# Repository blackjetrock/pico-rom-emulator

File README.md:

# pico-rom-emulator
ROM Emulator using Pico

This is a ROM emulator using a Raspberry Pi Pico to do the emulation in firmware.
The emulator is a small program that presents data on 8 data lines depending on the state of 16 address lines.
As the emulation is done in firmware there is a limit to the speed of ROm that can be emulated.
This has been teste on a 900kHz 6303 system (Psion Organiser) and also a 2MHz 6502 system. It may be able to run faster
and with overclocking faster than the standard clock rate can handle. 
As emulation is in firmware you get an extra for free, namely an address tracing facility. It can be set to start on any address, all setup is done
using the code itself and the trace is accessed through a debugger, I use Eclipse.

The emulation currently runs on the second core of the RP2040, as I was having problems with the interrupts on core0 mucking up
the emulation, turning interrupts off was a problem as download didn't work well. Using core 1 seems to be a better solution. It may even be possible to 
run a USB serial monitor of some kind on core 0 while emulating. I haven't got round ot this yet.

There's a PCB in the repo too, which is a Pico and some level shifters to allow the emulator to run on a 5V system when the Pico is 3V3. The data direction
is under firmware control. I have been using the emulator configured with a hardware OE which menas the OE signal to the ROM goes to the CE of the level
shifters. Placing data on the bus is therefore under hardware control. The PCB can be configured in other ways but I've not tried that.

This is a work in progress, but I have used it to get traces for stuff I've been working on.

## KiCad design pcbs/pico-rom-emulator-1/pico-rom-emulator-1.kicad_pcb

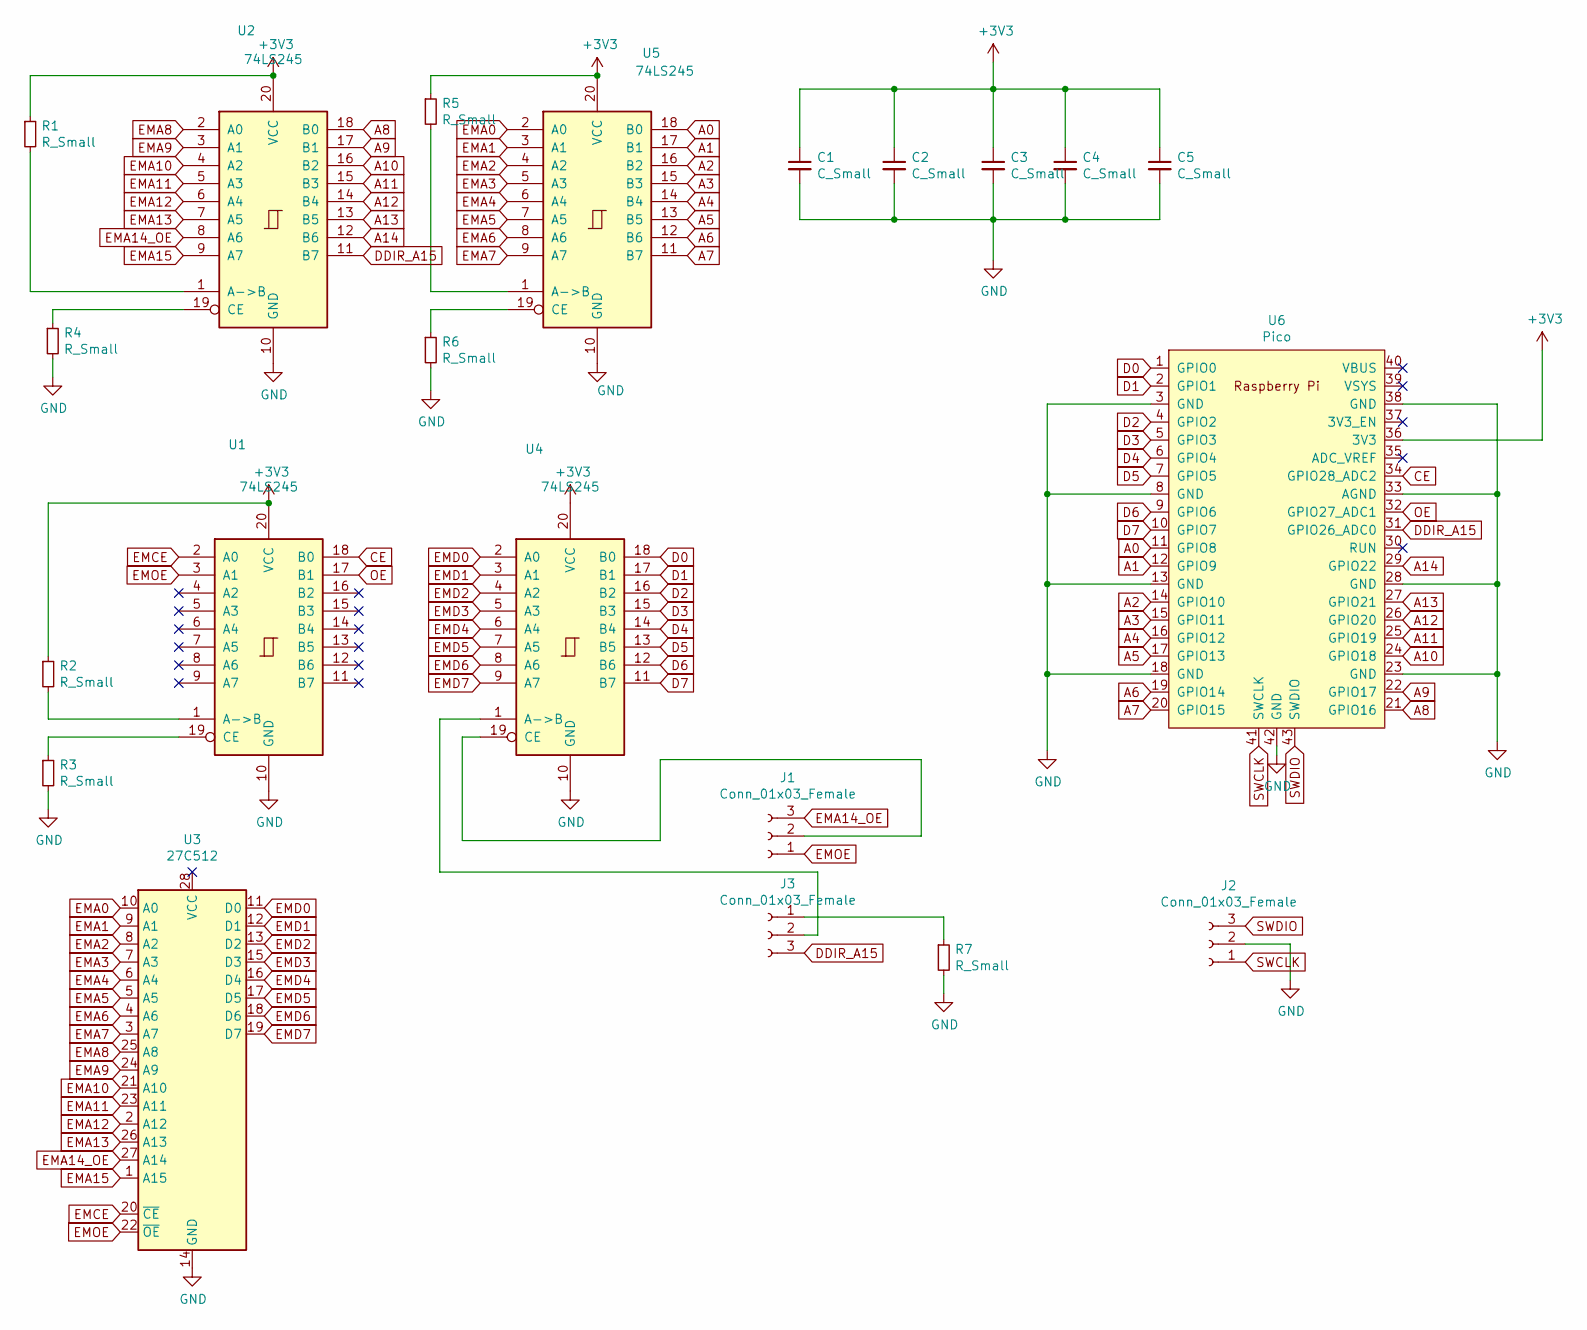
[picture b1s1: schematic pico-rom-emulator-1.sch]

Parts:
C1, C2, C3, C4, C5: C_Small; C_0805_2012Metric_Pad1.15x1.40mm_HandSolder
J1, J2, J3: Conn_01x03_Female; PinHeader_1x03_P2.54mm_Vertical
R1, R2, R3, R4, R5, R6, R7: R_Small; R_0805_2012Metric_Pad1.15x1.40mm_HandSolder
U1, U2, U4, U5: 74LS245; SOIC-20W_7.5x12.8mm_P1.27mm
U3: 27C512; DIP-28_W15.24mm
U6: Pico; RPi_Pico_SMD_TH

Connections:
+3V3: C1.1, C2.1, C3.1, C4.1, C5.1, R1.1, R2.1, R5.1, U1.20 (VCC), U2.20 (VCC), U4.20 (VCC), U5.20 (VCC), U6.36 (3V3)
A0: U5.18 (B0), U6.11 (GPIO8)
A1: U5.17 (B1), U6.12 (GPIO9)
A2: U5.16 (B2), U6.14 (GPIO10)
A3: U5.15 (B3), U6.15 (GPIO11)
A4: U5.14 (B4), U6.16 (GPIO12)
A5: U5.13 (B5), U6.17 (GPIO13)
A6: U5.12 (B6), U6.19 (GPIO14)
A7: U5.11 (B7), U6.20 (GPIO15)
A8: U2.18 (B0), U6.21 (GPIO16)
A9: U2.17 (B1), U6.22 (GPIO17)
A10: U2.16 (B2), U6.24 (GPIO18)
A11: U2.15 (B3), U6.25 (GPIO19)
A12: U2.14 (B4), U6.26 (GPIO20)
A13: U2.13 (B5), U6.27 (GPIO21)
A14: U2.12 (B6), U6.29 (GPIO22)
CE: U1.18 (B0), U6.34 (GPIO28_ADC2)
D0: U4.18 (B0), U6.1 (GPIO0)
D1: U4.17 (B1), U6.2 (GPIO1)
D2: U4.16 (B2), U6.4 (GPIO2)
D3: U4.15 (B3), U6.5 (GPIO3)
D4: U4.14 (B4), U6.6 (GPIO4)
D5: U4.13 (B5), U6.7 (GPIO5)
D6: U4.12 (B6), U6.9 (GPIO6)
D7: U4.11 (B7), U6.10 (GPIO7)
DDIR_A15: J3.3, U2.11 (B7), U6.31 (GPIO26_ADC0)
EMA0: U3.10 (A0), U5.2 (A0)
EMA1: U3.9 (A1), U5.3 (A1)
EMA2: U3.8 (A2), U5.4 (A2)
EMA3: U3.7 (A3), U5.5 (A3)
EMA4: U3.6 (A4), U5.6 (A4)
EMA5: U3.5 (A5), U5.7 (A5)
EMA6: U3.4 (A6), U5.8 (A6)
EMA7: U3.3 (A7), U5.9 (A7)
EMA8: U2.2 (A0), U3.25 (A8)
EMA9: U2.3 (A1), U3.24 (A9)
EMA10: U2.4 (A2), U3.21 (A10)
EMA11: U2.5 (A3), U3.23 (A11)
EMA12: U2.6 (A4), U3.2 (A12)
EMA13: U2.7 (A5), U3.26 (A13)
EMA14_OE: J1.3, U2.8 (A6), U3.27 (A14)
EMA15: U2.9 (A7), U3.1 (A15)
EMCE: U1.2 (A0), U3.20 (~CE)
EMD0: U3.11 (D0), U4.2 (A0)
EMD1: U3.12 (D1), U4.3 (A1)
EMD2: U3.13 (D2), U4.4 (A2)
EMD3: U3.15 (D3), U4.5 (A3)
EMD4: U3.16 (D4), U4.6 (A4)
EMD5: U3.17 (D5), U4.7 (A5)
EMD6: U3.18 (D6), U4.8 (A6)
EMD7: U3.19 (D7), U4.9 (A7)
EMOE: J1.1, U1.3 (A1), U3.22 (~OE)
GND: C1.2, C2.2, C3.2, C4.2, C5.2, J2.2, R3.2, R4.2, R6.2, R7.2, U1.10 (GND), U2.10 (GND), U3.14 (GND), U4.10 (GND), U5.10 (GND), U6.3 (GND), U6.8 (GND), U6.13 (GND), U6.18 (GND), U6.23 (GND), U6.28 (GND), U6.33 (AGND), U6.38 (GND), U6.42 (GND)
unnamed: J1.2, U4.19 (CE)
unnamed: J3.1, R7.1
unnamed: J3.2, U4.1 (A->B)
unnamed: R1.2, U2.1 (A->B)
unnamed: R2.2, U1.1 (A->B)
unnamed: R3.1, U1.19 (CE)
unnamed: R4.1, U2.19 (CE)
unnamed: R5.2, U5.1 (A->B)
unnamed: R6.1, U5.19 (CE)
OE: U1.17 (B1), U6.32 (GPIO27_ADC1)
SWCLK: J2.1, U6.41 (SWCLK)
SWDIO: J2.3, U6.43 (SWDIO)

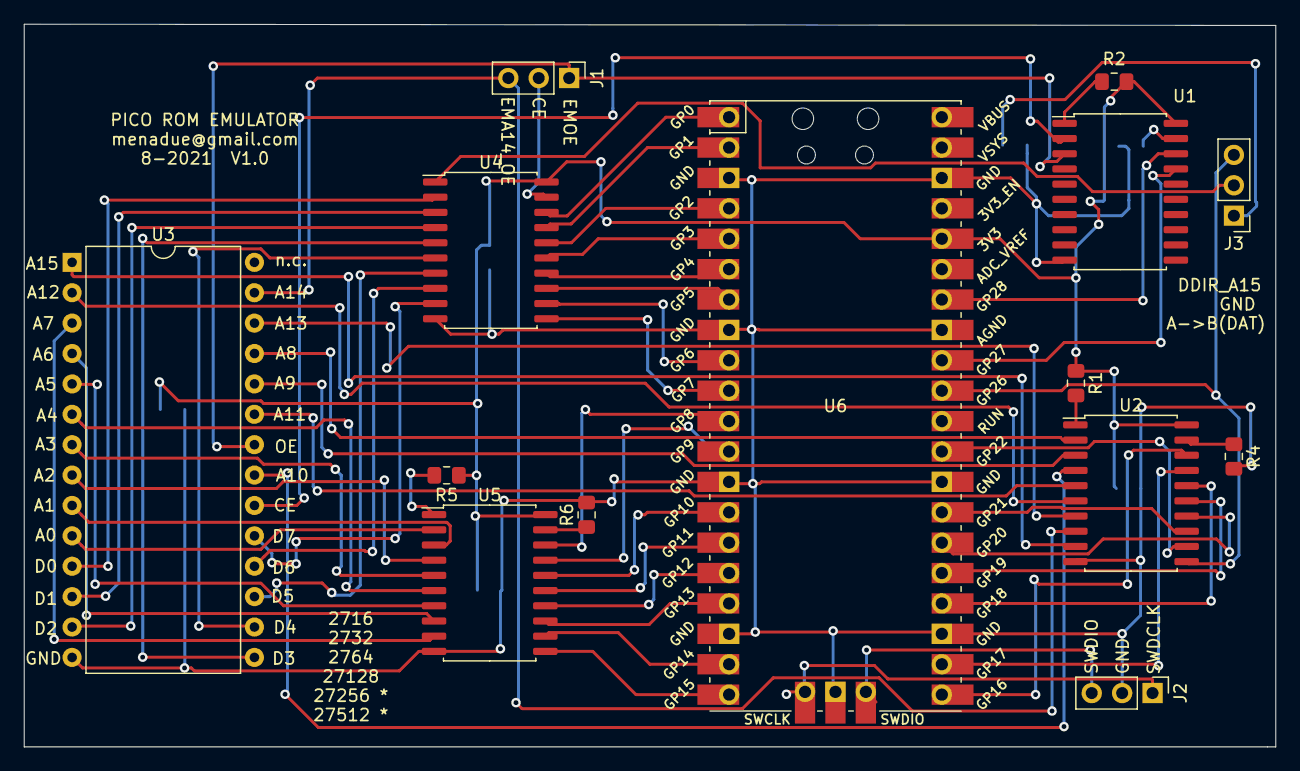
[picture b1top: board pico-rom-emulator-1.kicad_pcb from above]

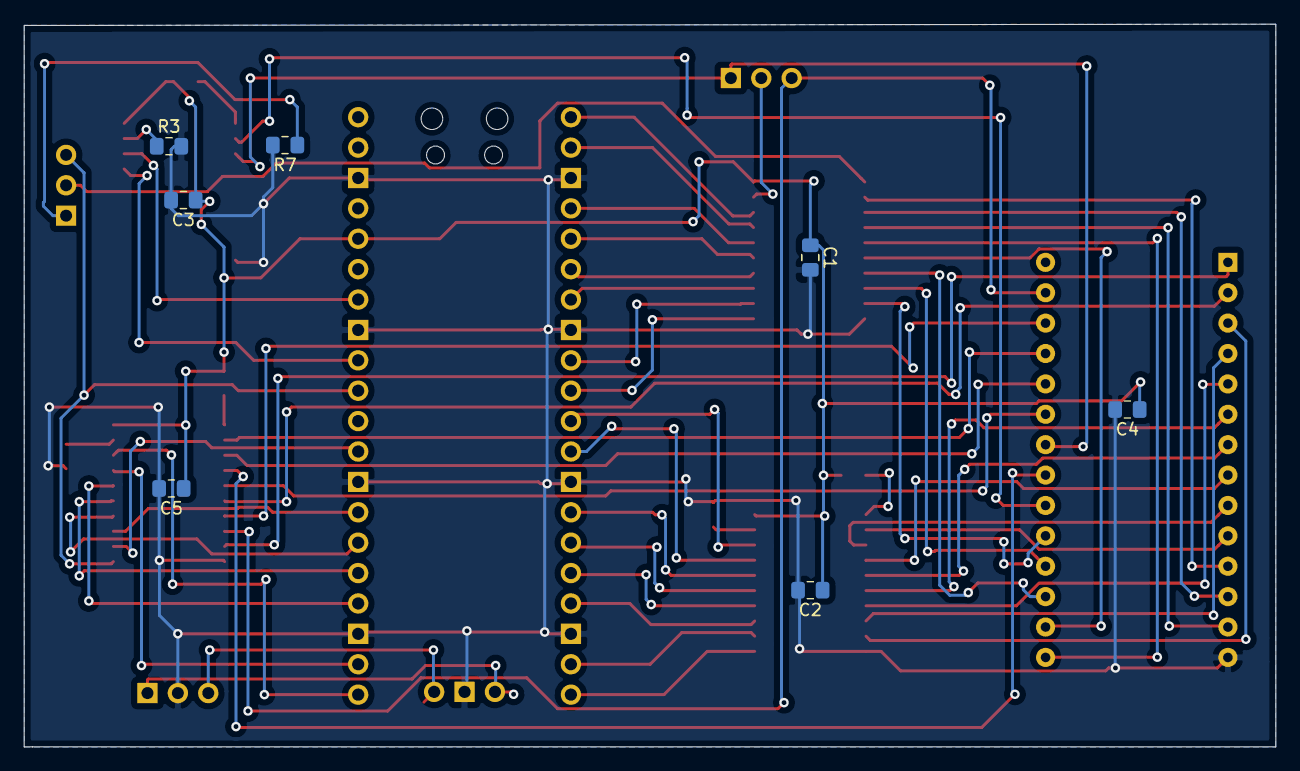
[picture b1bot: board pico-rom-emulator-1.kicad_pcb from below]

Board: 2 copper layers, 104.6 x 60.4 mm, 21 parts (7 on the bottom side), 65 nets.

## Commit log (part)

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2021-08-20 Initial check in
2021-08-20 PCB updates
2021-10-23 Added C code for emulator
